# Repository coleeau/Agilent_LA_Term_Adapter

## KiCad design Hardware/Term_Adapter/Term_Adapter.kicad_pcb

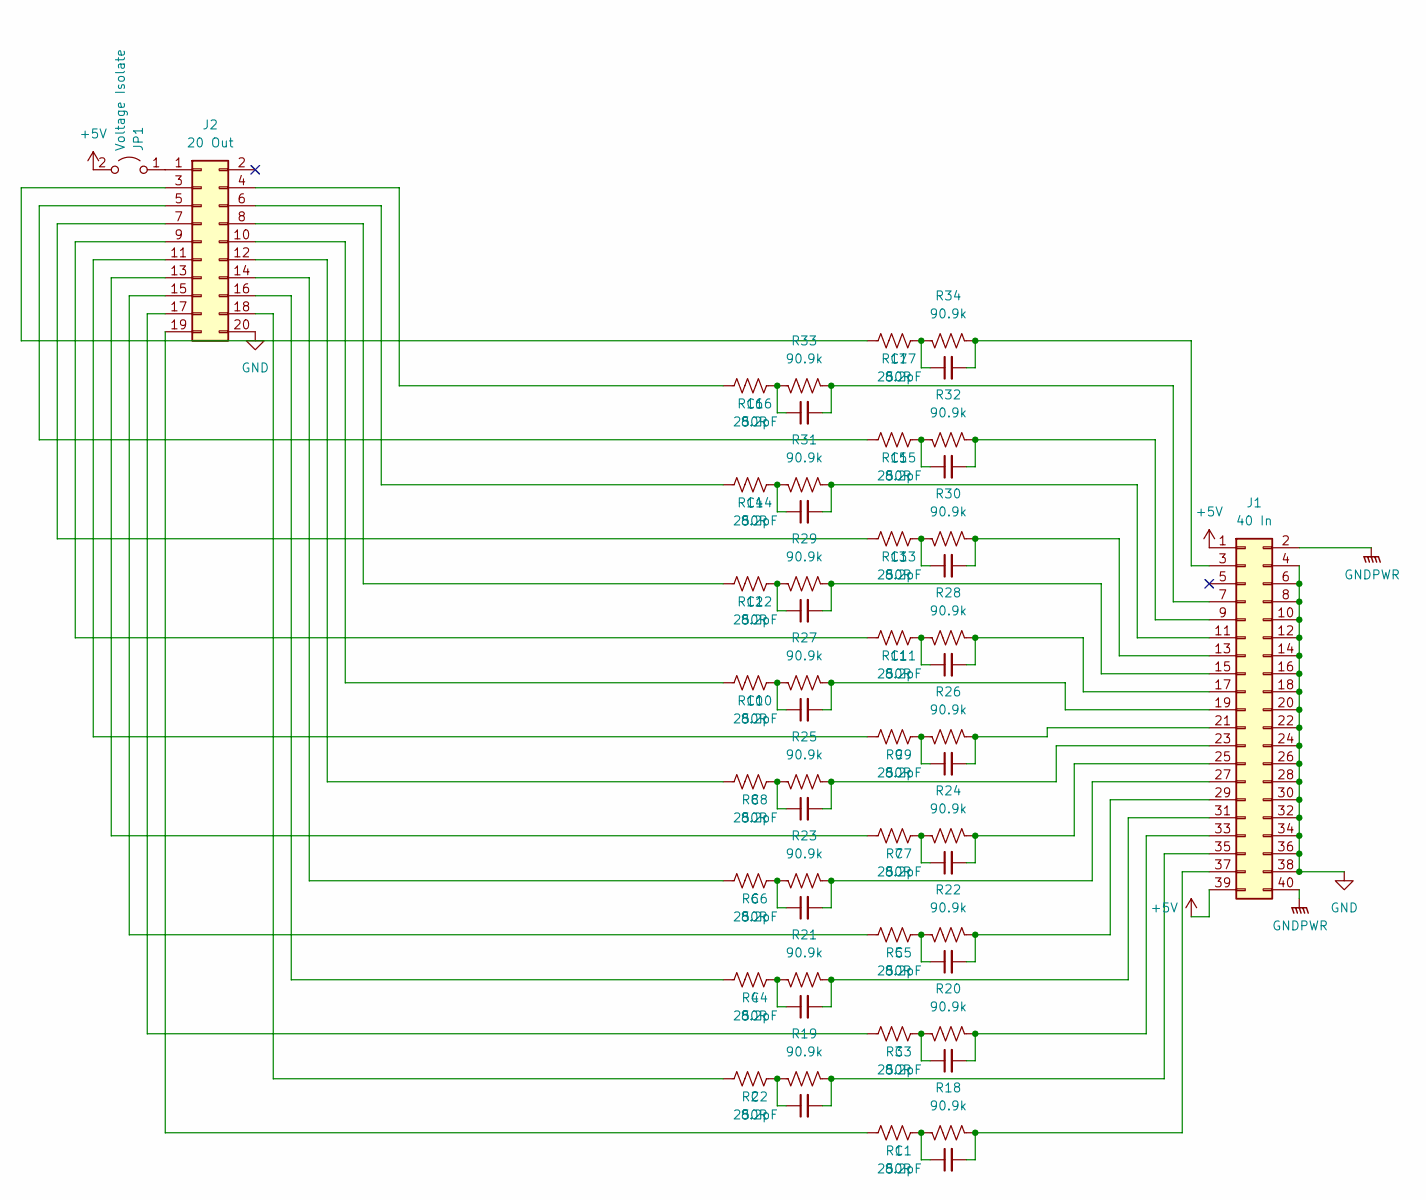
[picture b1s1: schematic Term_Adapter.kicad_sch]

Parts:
C1, C2, C3, C4, C5, C6, C7, C8, C9, C10, C11, C12, C13, C14, C15, C16, C17: 8.2pF; R_0603_1608Metric
J1: 40 In; SHDRRA40W64P254_2X20_5840X930X878P
J2: 20 Out; CONN20_D10-RA-BK_SUL
JP1: Voltage Isolate; PinHeader_1x02_P2.54mm_Horizontal
R1, R2, R3, R4, R5, R6, R7, R8, R9, R10, R11, R12, R13, R14, R15, R16, R17: 250R; R_0603_1608Metric
R18, R19, R20, R21, R22, R23, R24, R25, R26, R27, R28, R29, R30, R31, R32, R33, R34: 90.9k; R_0603_1608Metric

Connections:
+5V: J1.1, J1.39, JP1.2 (B)
GND: J1.4, J1.6, J1.8, J1.10, J1.12, J1.14, J1.16, J1.18, J1.20, J1.22, J1.24, J1.26, J1.28, J1.30, J1.32, J1.34, J1.36, J1.38, J2.20
GNDPWR: J1.2, J1.40
unnamed: C1.1, R1.2, R18.2
unnamed: C2.1, R2.2, R19.2
unnamed: C3.1, R3.2, R20.2
unnamed: C4.1, R4.2, R21.2
unnamed: C5.1, R5.2, R22.2
unnamed: C6.1, R6.2, R23.2
unnamed: C7.1, R7.2, R24.2
unnamed: C8.1, R8.2, R25.2
unnamed: C9.1, R9.2, R26.2
unnamed: C10.1, R10.2, R27.2
unnamed: C11.1, R11.2, R28.2
unnamed: C12.1, R12.2, R29.2
unnamed: C13.1, R13.2, R30.2
unnamed: C14.1, R14.2, R31.2
unnamed: C15.1, R15.2, R32.2
unnamed: C16.1, R16.2, R33.2
unnamed: C17.1, R17.2, R34.2
unnamed: C17.2, J1.3, R34.1
unnamed: C16.2, J1.7, R33.1
unnamed: C15.2, J1.9, R32.1
unnamed: C14.2, J1.11, R31.1
unnamed: C13.2, J1.13, R30.1
unnamed: C12.2, J1.15, R29.1
unnamed: C11.2, J1.17, R28.1
unnamed: C10.2, J1.19, R27.1
unnamed: C9.2, J1.21, R26.1
unnamed: C8.2, J1.23, R25.1
unnamed: C7.2, J1.25, R24.1
unnamed: C6.2, J1.27, R23.1
unnamed: C5.2, J1.29, R22.1
unnamed: C4.2, J1.31, R21.1
unnamed: C3.2, J1.33, R20.1
unnamed: C2.2, J1.35, R19.1
unnamed: C1.2, J1.37, R18.1
unnamed: J2.1, JP1.1 (A)
unnamed: J2.3, R17.1
unnamed: J2.4, R16.1
unnamed: J2.5, R15.1
unnamed: J2.6, R14.1
unnamed: J2.7, R13.1
unnamed: J2.8, R12.1
unnamed: J2.9, R11.1
unnamed: J2.10, R10.1
unnamed: J2.11, R9.1
unnamed: J2.12, R8.1
unnamed: J2.13, R7.1
unnamed: J2.14, R6.1
unnamed: J2.15, R5.1
unnamed: J2.16, R4.1
unnamed: J2.17, R3.1
unnamed: J2.18, R2.1
unnamed: J2.19, R1.1

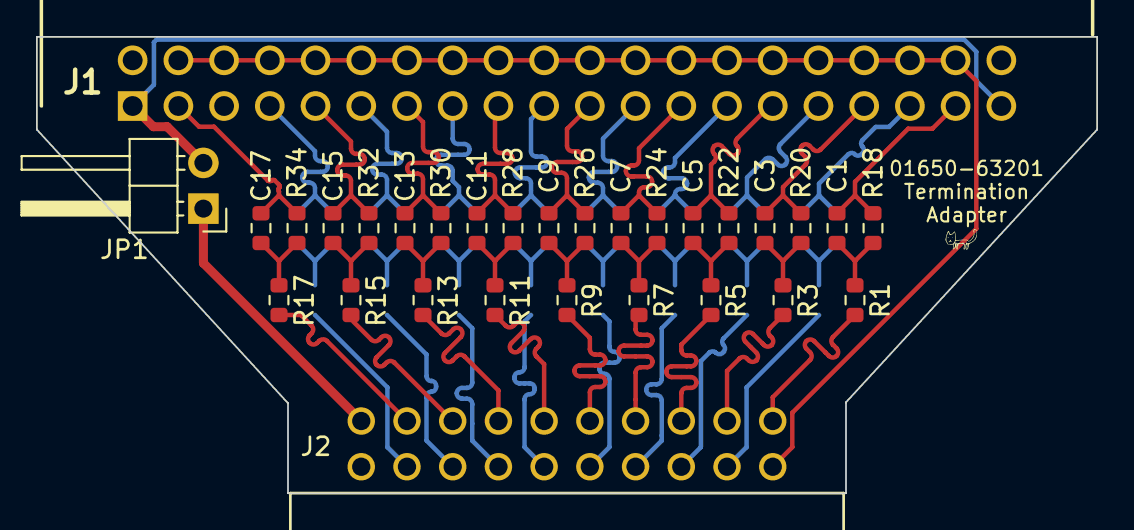
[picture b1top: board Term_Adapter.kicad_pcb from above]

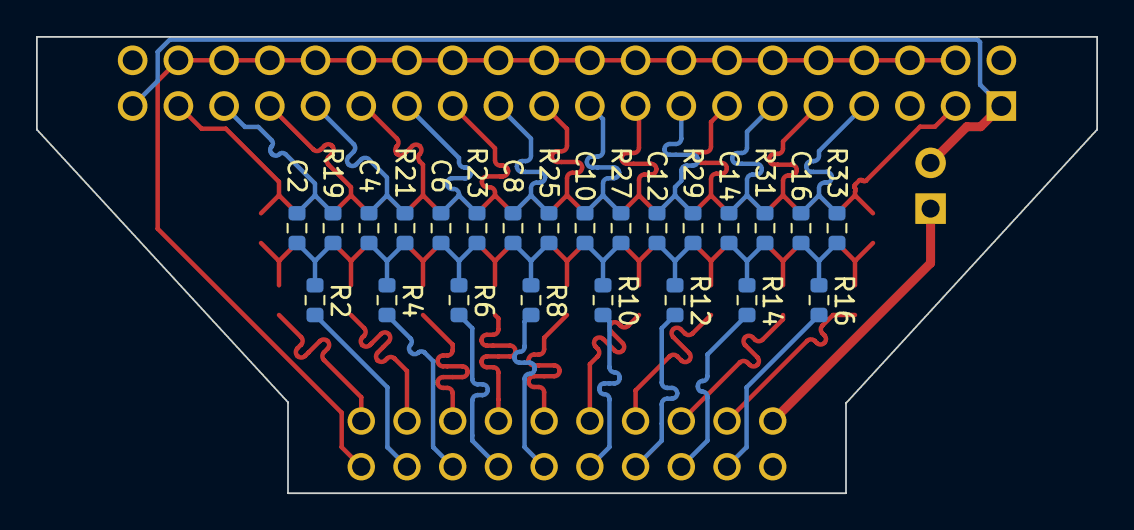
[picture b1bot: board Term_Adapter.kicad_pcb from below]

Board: 2 copper layers, 58.9 x 25.4 mm, 54 parts (24 on the bottom side), 55 nets.

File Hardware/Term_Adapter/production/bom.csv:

Designator,Footprint,Quantity,Value,LCSC Part #
"C1, C10, C11, C12, C13, C14, C15, C16, C17, C2, C3, C4, C5, C6, C7, C8, C9",0603,17,8.2pF,
J1,SHDRRA40W64P254_2X20_5840X930X878P,1,40 In,
J2,CONN20_D10-RA-BK_SUL,1,20 Out,
JP1,PinHeader_1x02_P2.54mm_Horizontal,1,Voltage Isolate,
"R1, R10, R11, R12, R13, R14, R15, R16, R17, R2, R3, R4, R5, R6, R7, R8, R9",0603,17,250R,
"R18, R19, R20, R21, R22, R23, R24, R25, R26, R27, R28, R29, R30, R31, R32, R33, R34",0603,17,90.9k,

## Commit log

2024-07-15 Initial
